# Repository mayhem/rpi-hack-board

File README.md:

# rpi-hack-board
A Raspberry Pi Zero/Zero-w prototyping/hacking board for common circuits and connections

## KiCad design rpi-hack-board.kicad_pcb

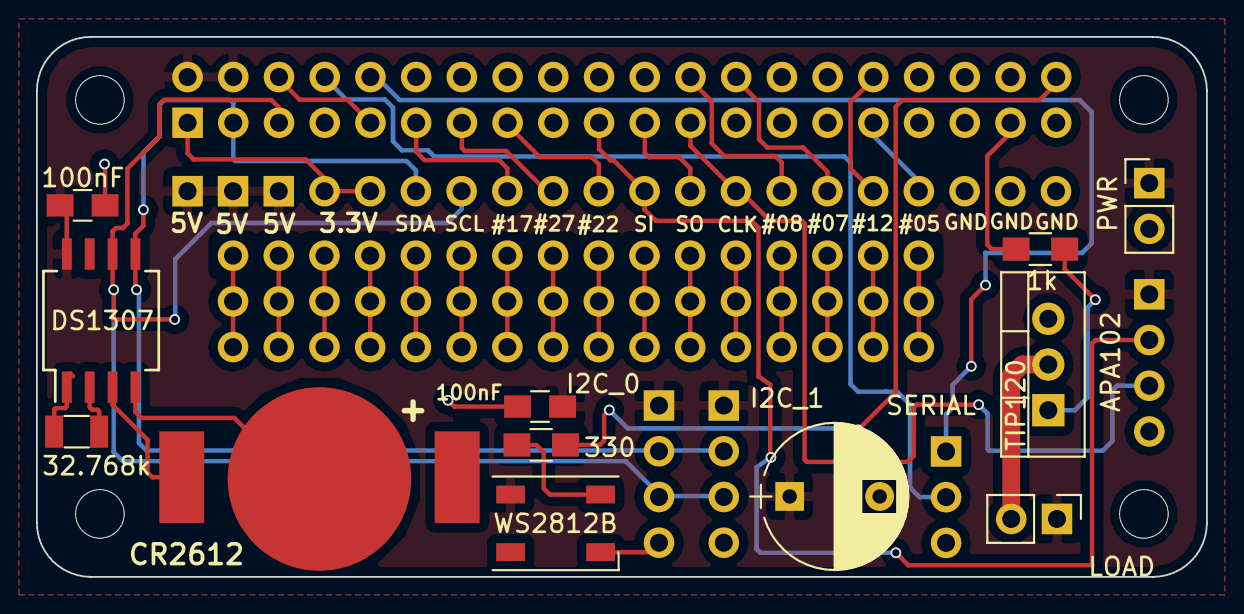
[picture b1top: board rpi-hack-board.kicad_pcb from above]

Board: 2 copper layers, 65.0 x 30.0 mm, 18 parts (0 on the bottom side), 26 nets.

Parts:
BT1: Battery_Cell; BAT_CR1216
C1: CP; CP_Radial_D8.0mm_P5.00mm
C2, C3: 100nF; C_0805_HandSoldering
J1: LOAD; Screw_Terminal_Vertical_1x02_Pitch2.54mm
J2: I2C_0; Pin_Header_Straight_1x04_Pitch2.54mm
J3: I2C_1; Pin_Header_Straight_1x04_Pitch2.54mm
J4: Raspberry_Pi_2_3; Pin_Header_Straight_2x20_Pitch2.54mm
J5: PWR; Screw_Terminal_Vertical_1x02_Pitch2.54mm
J6: APA102; Pin_Header_Straight_1x04_Pitch2.54mm
J7: SERIAL; Pin_Header_Straight_1x03_Pitch2.54mm
J8: BREAKOUTS; Pin_Header_Straight_1x20_Pitch2.54mm
LED1: WS2812B; LED_WS2812B-PLCC4
Q1: TIP120; TO-220-3_Vertical
R1: 1k; R_0805_HandSoldering
R2: 330; R_0805_HandSoldering
U1: DS1307; SO-8_5.3x6.2mm_Pitch1.27mm
X1: 32.768k; Crystal_SMD_3215-2pin_3.2x1.5mm

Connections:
/3.3V: J4.1, J8.4, J8.5
/5V: C1.1, C2.1, C3.1, J1.1, J2.1, J3.1, J4.2, J4.4, J5.1, J6.1, J8.1, J8.2, J8.3, LED1.1, U1.8
/GPIO6: J4.31, J8.17
/GPIO07: J4.26, J8.15
/GPIO08: J4.24, J8.14
/GPIO12: J4.32, J8.16
/GPIO17: J4.11, J8.8
/GPIO22: J4.15, J8.10
/GPIO27: J4.13, J8.9
/LOAD_DRV: J4.37, R1.2
/MISO: J4.21, J8.12
/MOSI: J4.19, J6.2, J8.11
/RX: J4.10, J7.1
/SCL: J2.3, J3.3, J4.5, J8.7, U1.6
/SCLK: J4.23, J6.3, J8.13
/SDA: J2.2, J3.2, J4.3, J8.6, U1.5
/TX: J4.8, J7.2
/WS2812: J4.40, R2.1
GND: C1.2, C2.2, C3.2, J2.4, J3.4, J4.6, J4.9, J4.14, J4.20, J4.25, J4.30, J4.34, J4.39, J5.2, J6.4, J7.3, J8.18, J8.19, J8.20, LED1.3, Q1.3
unnamed: BT1.1, U1.3
unnamed: BT1.2, U1.4
unnamed: J1.2, Q1.2
unnamed: LED1.4, R2.2
unnamed: Q1.1, R1.1
unnamed: U1.1, X1.1
unnamed: U1.2, X1.2

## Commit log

2017-11-25 First cut at schematic is done
2017-11-26 Schematic nearly finished, started layout
2017-11-27 Layout nearly done, interim check-in
2017-11-27 Getting closer, but still needs more work
2017-11-28 SOOOOO CLOSE!
2017-11-28 Layout is complete, remaining connections are not needed!
2017-11-28 Minor cleanup
2017-11-28 Got a good start on the silkscreen layer, but there is loads to do.
2017-11-29 Connected all the prototyping lines
2017-11-29 Most of the silkscreen looks good now
2017-11-29 Might be done!!
